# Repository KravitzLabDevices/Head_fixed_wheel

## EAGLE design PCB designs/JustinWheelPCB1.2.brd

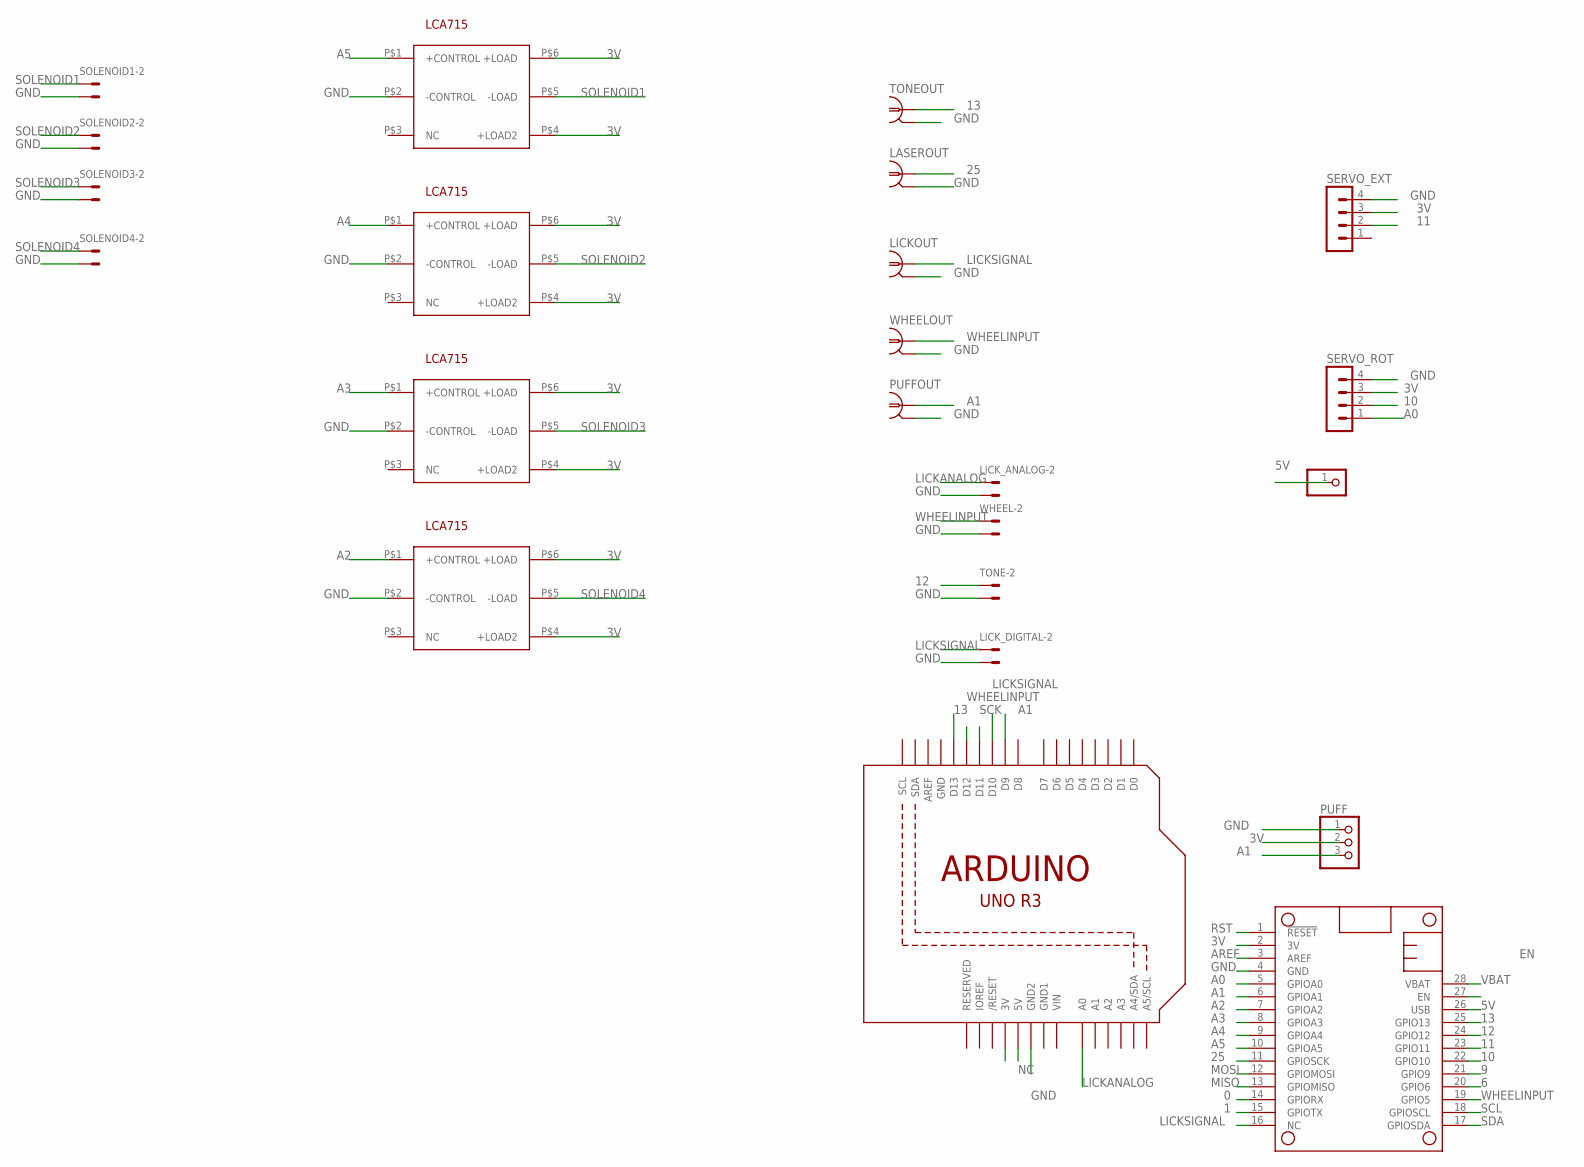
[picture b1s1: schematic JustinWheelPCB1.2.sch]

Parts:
JP1: PINHD-1X1; 1X01
LASEROUT: 1-227161-0; AMP_227161
LICKOUT: 1-227161-0; AMP_227161
LICK_ANALOG: 22-23-2021
LICK_DIGITAL: 22-23-2021
MS2: MICROSHIELD_NODIM; MICROSHIELD_DIM
PUFF: PINHD-1X3; 1X03
PUFFOUT: 1-227161-0; AMP_227161
SERVO_EXT: MA04-1
SERVO_ROT: MA04-1
SOL1, SOL2, SOL3, SOL4: LCA715S; LCA7XX
SOLENOID1, SOLENOID2, SOLENOID3, SOLENOID4: 22-23-2021
TONE: 22-23-2021
TONEOUT: 1-227161-0; AMP_227161
U1: ARDUINOR3-BPLACE
WHEEL: 22-23-2021
WHEELOUT: 1-227161-0; AMP_227161

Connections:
0: MS2.14 (GPIORX)
1: MS2.15 (GPIOTX)
3V: MS2.2 (3V), PUFF.2, SERVO_EXT.3, SERVO_ROT.3, SOL1.P$4 (+LOAD2), SOL1.P$6 (+LOAD), SOL2.P$4 (+LOAD2), SOL2.P$6 (+LOAD), SOL3.P$4 (+LOAD2), SOL3.P$6 (+LOAD), SOL4.P$4 (+LOAD2), SOL4.P$6 (+LOAD)
5V: JP1.1, MS2.26 (USB)
6: MS2.20 (GPIO6)
9: MS2.21 (GPIO9)
10: MS2.22 (GPIO10), SERVO_ROT.2
11: MS2.23 (GPIO11), SERVO_EXT.2
12: MS2.24 (GPIO12), TONE.1
13: MS2.25 (GPIO13), TONEOUT.1, U1.D13
25: LASEROUT.1, MS2.11 (GPIOSCK)
A0: MS2.5 (GPIOA0), SERVO_ROT.1
A1: MS2.6 (GPIOA1), PUFF.3, PUFFOUT.1, U1.D9
A2: MS2.7 (GPIOA2), SOL4.P$1 (+CONTROL)
A3: MS2.8 (GPIOA3), SOL3.P$1 (+CONTROL)
A4: MS2.9 (GPIOA4), SOL2.P$1 (+CONTROL)
A5: MS2.10 (GPIOA5), SOL1.P$1 (+CONTROL)
AREF: MS2.3 (AREF)
EN: MS2.27 (EN)
GND: LASEROUT.2, LICKOUT.2, LICK_ANALOG.2, LICK_DIGITAL.2, MS2.4 (GND), PUFF.1, PUFFOUT.2, SERVO_EXT.4, SERVO_ROT.4, SOL1.P$2 (-CONTROL), SOL2.P$2 (-CONTROL), SOL3.P$2 (-CONTROL), SOL4.P$2 (-CONTROL), SOLENOID1.2, SOLENOID2.2, SOLENOID3.2, SOLENOID4.2, TONE.2, TONEOUT.2, U1.GND, U1.GND2, WHEEL.2, WHEELOUT.2
GND1: U1.GND1
LICKANALOG: LICK_ANALOG.1, U1.A0
LICKSIGNAL: LICKOUT.1, LICK_DIGITAL.1, MS2.16 (NC), U1.D10
MISO: MS2.13 (GPIOMISO)
MOSI: MS2.12 (GPIOMOSI)
NC: U1.5V
RST: MS2.1 (!RESET)
SCK: U1.D11
SCL: MS2.18 (GPIOSCL)
SDA: MS2.17 (GPIOSDA)
SOLENOID1: SOL1.P$5 (-LOAD), SOLENOID1.1
SOLENOID2: SOL2.P$5 (-LOAD), SOLENOID2.1
SOLENOID3: SOL3.P$5 (-LOAD), SOLENOID3.1
SOLENOID4: SOL4.P$5 (-LOAD), SOLENOID4.1
VBAT: MS2.28 (VBAT)
VIN: U1.VIN
WHEELINPUT: MS2.19 (GPIO5), U1.D12, WHEEL.1, WHEELOUT.1

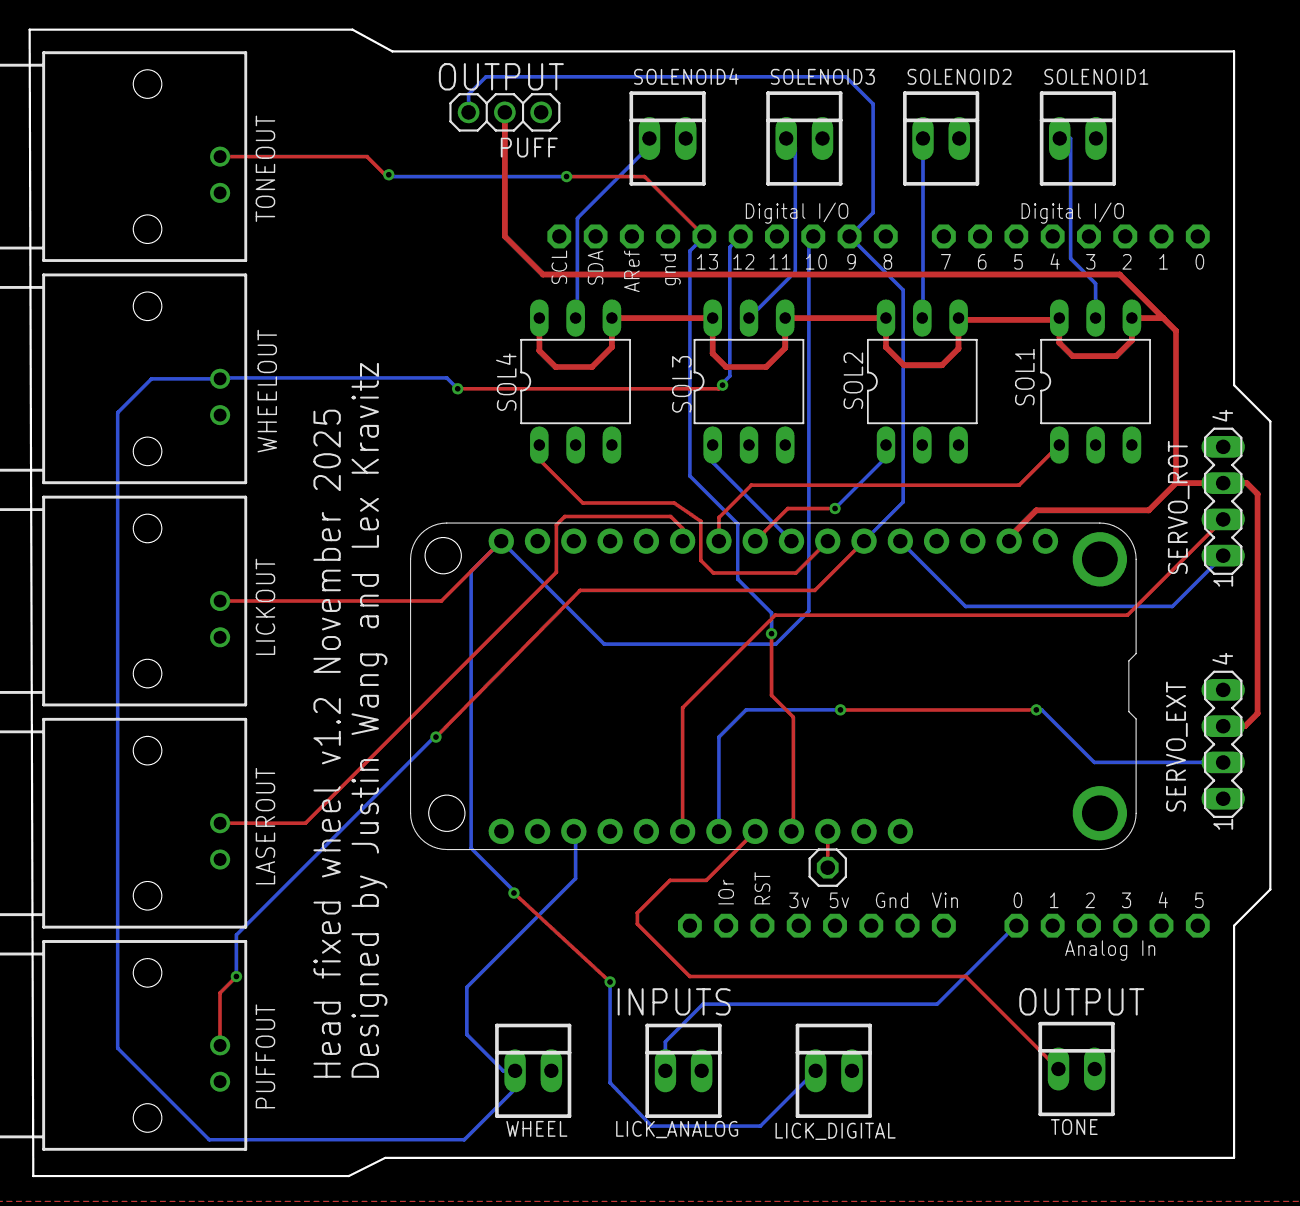
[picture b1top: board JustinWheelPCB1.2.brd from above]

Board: 2 copper layers, 86.9 x 80.3 mm, 23 parts (0 on the bottom side), 21 nets.

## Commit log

2025-12-03 Add JustinWheelPCB v1.2 board and schematic files
    Initial commit of the JustinWheelPCB version 1.2 Eagle board (.brd) and schematic (.sch) files. These files define the PCB layout and circuit design for the head fixed wheel project.
2025-12-03 Restructure project directories and remove unused files
    Moved Arduino libraries, Bonsai code, and PCB designs to new organized directories. Renamed main lickometer code file. Deleted multiple unused Arduino code modules, header files, and setup documentat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
2025-12-03 Add README files for KB2040 and M4 control code
    Added initial README.md files to the KB2040_Wheel_Encoder and M4_Control_Code directories, providing a brief description of the 5-spout sipper device for head-fixed mouse experiments.
